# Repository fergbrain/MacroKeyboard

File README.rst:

.. |ss| raw:: html

    <strike>

.. |se| raw:: html

    </strike>
******
README
******

This is the first successful PCB I've designed. I made it as part of `TeachMePCB's <https://www.teachmepcb.com>`_ PCB Layout 101 class.

Everyone in the course made a macrokeypad of some sort. The core "requirements" were:

* 10 MX-style key switches
* 2 Rotary Encoders with RGB leds
* VEML7700 Ambient Light Sensor (I2C)
* NLSF595 LED Driver (SPI)
* 10 NeoPixel lights (1-wire)
* Don't make a rectangular PCB
* Raspberry Pi Pico microcontroller

I made a couple of changes:

* Swapped PCA9745B for NLSF595
* Added ePaper display (because why not make my first project harder)

Required Libraries
==================
* Standard CircuitPython
* Adafruit CircuitPython Library
    * adafruit_hid
    * adafruit_led_animation
    * adafruit_debouncer
    * adafruit_veml7700
    * adafruit_display_text
    * adafruit_button
* `fergcorp_pca9745b <https://github.com/fergbrain/Fergcorp_CircuitPython_PCA9745B>`_
* `fergcorp_pdispectra <https://github.com/fergbrain/Fergcorp_CircuitPython_PDISpectra>`_

Build Notes and Errata:
=======================
For P/N 21-11.03-3, Rev NEW
---------------------------
**Last updated: 2 Feb 2022**

R1 (c5022a6)
^^^^^^^^^^^^

U401 (PI4ULS5V201TAEX), Pin 6:

* IS: Connected to ground.
* SHOULD BE: Connected to 5V+ via a 4.7K ohm resistor

*Note: All annotations on the PCB were also reset and reassigned. However, the original annotation designations are used in this document.*

R2 (fcf9d7e)
^^^^^^^^^^^^
R2404, Pin 03 (SPI_MISO) of U2701 (PCA9745BTWJ)

* IS: Connected to SPI_MISO via R2704 (1k ohm)
* SHOULD BE: No resistor

Pin 27 (SPI_MOSI) of U2701 (PCA9745BTWJ)

* IS: Connected to SPI_MOSI via R2706 (1k ohm)
* SHOULD BE: No resistor

R2707, Pin 26 (SPI_SCLK) of U2701 (PCA9745BTWJ)

* IS: Connected to SPI_SCLK via R2707 (1k ohm)
* SHOULD BE: No resistor

R3 (bb8617a)
^^^^^^^^^^^^
S3001 (Rotary Encoder)

* IS: Pin 01 (red LED) and Pin 04 (blue LED) are swapped
    * S3001 Pin 01 (red LED) goes to U2701 Pin 13 (blue LED)
    * S3001 Pin 04 (blue LED) goes to U2701 Pin 11 (red LED)

* SHOULD BE:

    * S3001 Pin 01 (red LED) connects to 2701 Pin 11 (red LED)
    * S3001 Pin 04 (blue LED) to U2701 Pin 13 (blue LED)

*Note: This has been fixed in software for this version of the PCB*

R4 (3040ea1)
^^^^^^^^^^^^
J2901 (Connector for epaper) Pin 11 (Data/Command) and Pin 09 (Busy)

* IS:

    * U2801 Pin 15 labeled as GPIO12 and connects to J2901 Pin 11
    * U2801 Pin 16 is labeled as GPIO11 and connects to J2901 Pin 09

* SHOULD BE:

    * U2801 Pin 15 labeled as GPIO11 and connects to Pin 09
    * U2801 Pin 16 labeled as GPIO12 and connects to Pin 11

*Note: This has been fixed in software for this version of the PCB*

R5 (51e2212 / 8b634cf)
^^^^^^^^^^^^
* IS: R2901 is 470 ohms
* SHOULD BE: R2901 is 0.47 ohms

|ss| R6 (196a722) |se|
^^^^^^^^^^^^
* |ss|IS: J2901 (Connector for epaper) Pin 10 (Reset) connected to +3.3V via R2902 (100k ohm)|se|
* |ss|SHOULD BE: J2901 Pin 10 connected to U2801 Pin 14 (GPIO10)|se|
|ss|
*Note: This results in SWITCH 4 and ePaper Reset sharing a pin because there are no other pins available. The primary result is that careful context switching needs to managed in software to:*

1.	Deinitialize GPIO10 as an input for SWITCH 4
2.	Setup the ePaper display interface (which uses GPIO10 as an output)
3.	Perform whatever ePaper update is needed
4.	Deinitialze the ePaper interface (which deinitializes GPIO10 as an output)
5.	Re-initialize GPIO10 as an input for SWITCH 4

*Also, while the ePaper is not enabled (i.e. not initialized/reinitialized), GPIO17 (ePaper CS) needs to be set HIGH to prevent the ePaper controller from thinking that data on the SPI line is intended for it.*
|se|

R7 (80c609b)
^^^^^^^^^^^^
* IS: J2901 is Molex P/N 5052782433
* SHOULD BE: J2901 is Amphenol P/N F31L-1A7H1-11024

* IS: Component S201 and S3001 is SparkFun P/N COM-15141
* SHOULD BE: Bournes P/N PEL12T-4225S-S1024

*Note: COM-15141 was originally sourced as an alternate since the Bournes parts weren’t avaible. However, COM-15141 has quality control issues, including the Red LED not working well and the rotary action not registering correctly. SparkFun is aware of these issues.*

R8 (2cafc4d)
^^^^^^^^^^^^
* IS: J2901 (Connector for epaper) Pin 10 (Reset) connected to +3.3V via R2902 (100k ohm)
* SHOULD BE: J2901 Pin 10 connected to U2801 Pin 48 (GPIO25_LED aka TP5)

*Note: This replaces R6 in its entirety.*

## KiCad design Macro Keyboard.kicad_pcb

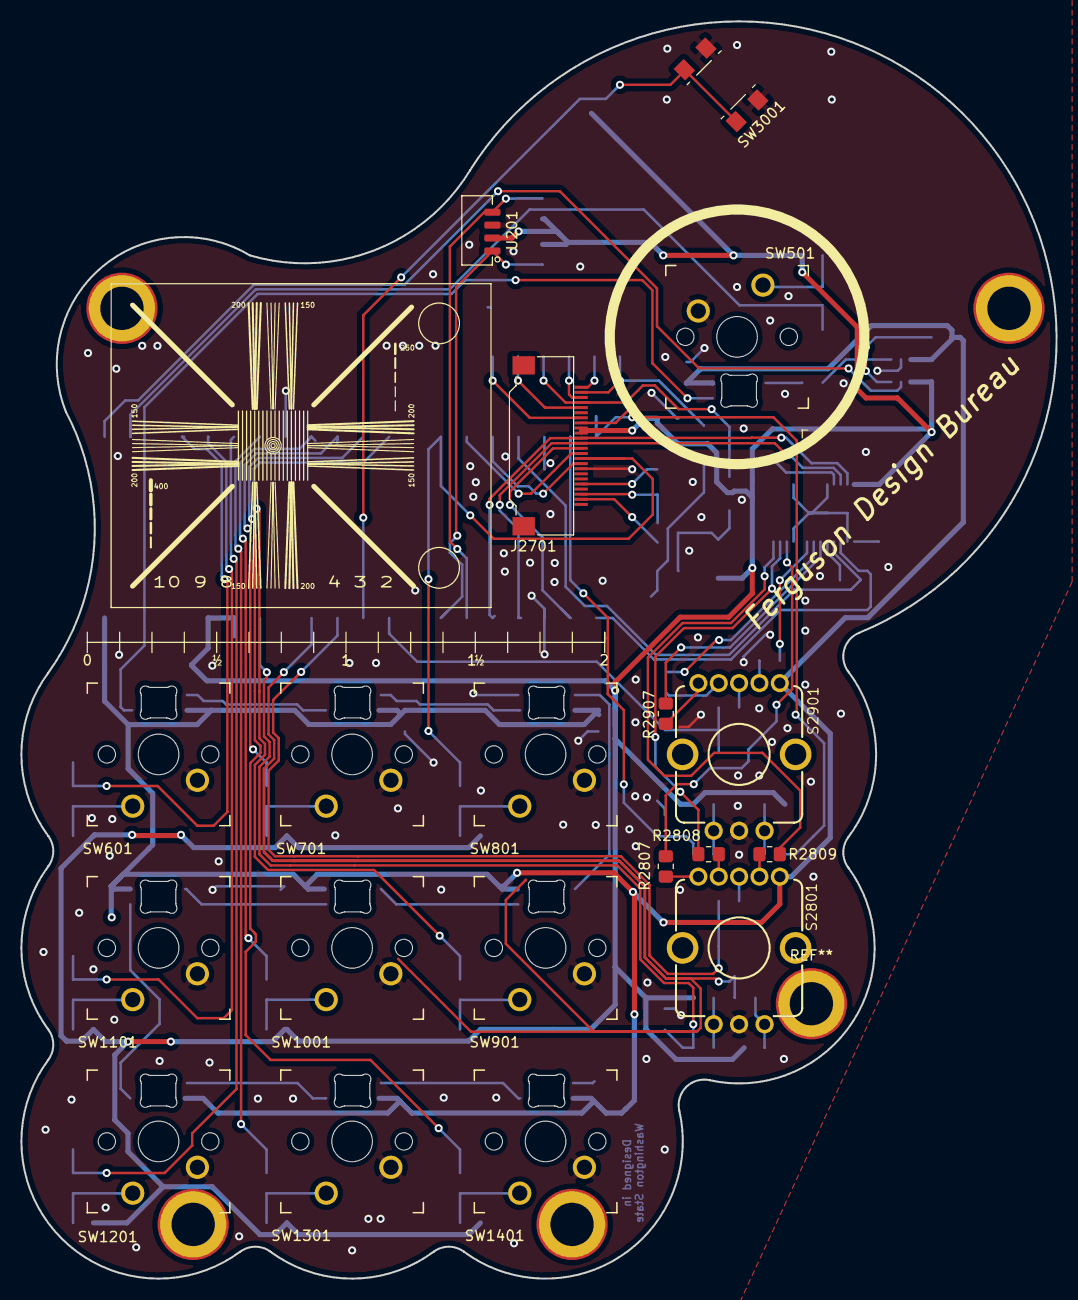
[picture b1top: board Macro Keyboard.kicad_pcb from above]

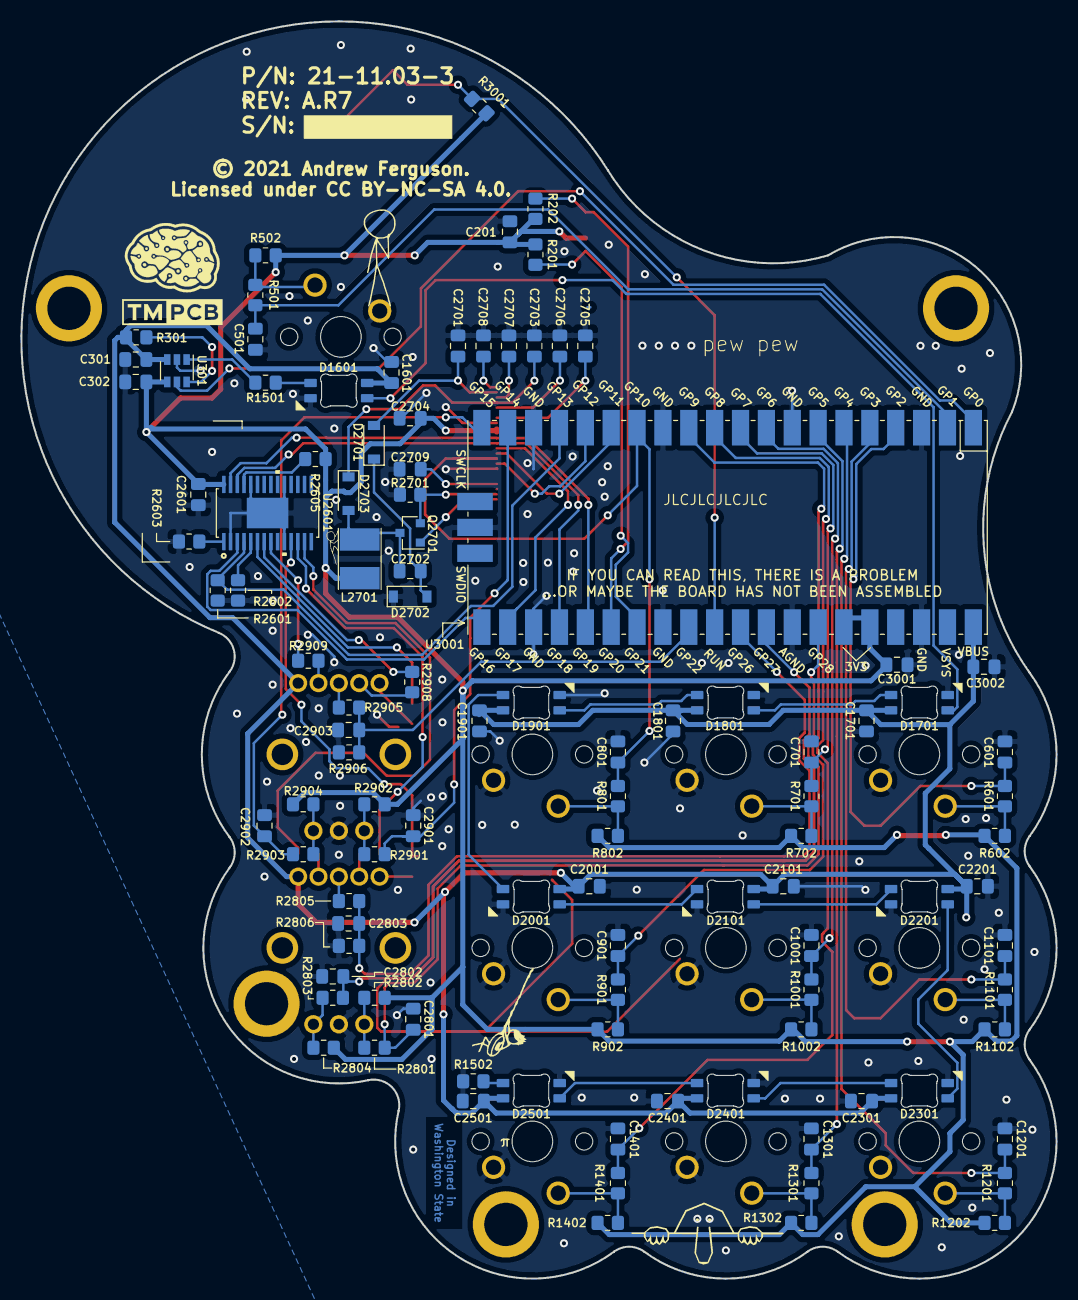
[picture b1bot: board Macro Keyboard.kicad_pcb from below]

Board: 2 copper layers, 101.6 x 123.4 mm, 129 parts (94 on the bottom side), 85 nets.

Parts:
C201, C1601, C1701, C1801, C1901, C2001, C2101, C2201, C2301, C2401, C2501: 10 uF 10% 10V; C_0805_2012Metric_Pad1.18x1.45mm_HandSolder
C301, C302, C501, C601, C701, C801, C901, C1001, C1101, C1201, C1301, C1401, C2601, C2701, C2703, C2704, C2705, C2706, C2707, C2708, C2709, C2801, C2802, C2803, C2901, C2902, C2903, C3001, C3002: 1 uF 10% 10V; C_0805_2012Metric_Pad1.18x1.45mm_HandSolder
C2702: 4.7 uF 10% 10V; C_0805_2012Metric_Pad1.18x1.45mm_HandSolder
D1601, D1701, D1801, D1901, D2301, D2401, D2501: SK6812MINI-E; MX_SK6812MINI-E
D2001, D2101, D2201: SK6812MINI-E; MX_SK6812MINI-E_REV
D2701, D2702, D2703: MBR0530; D_SOD-123
DS**: e-paper_E2154FS091
J2701: FPC 1x24; Amphenol_F31L-1A7H1-11024
L2701: 10 uH 20% 0.8A; L_Taiyo-Yuden_NR-40xx_HandSoldering
Q2701: Q_PJFET_GDS; SOT-23
R201, R202, R301, R501, R601, R701, R801, R901, R1001, R1101, R1201, R1301, R1401, R2601, R2801, R2803, R2806, R2901, R2903, R2906, R3001: 4.7k 5%; R_0805_2012Metric_Pad1.20x1.40mm_HandSolder
R502, R602, R702, R802, R902, R1002, R1102, R1202, R1302, R1402, R2802, R2804, R2902, R2904: 47k 5%; R_0805_2012Metric_Pad1.20x1.40mm_HandSolder
R1501, R2807, R2907: 150 5%; R_0805_2012Metric_Pad1.20x1.40mm_HandSolder
R1502, R2805, R2905: 2.7k 5%; R_0805_2012Metric_Pad1.20x1.40mm_HandSolder
R2602, R2603: 1k 5%; R_0805_2012Metric_Pad1.20x1.40mm_HandSolder
R2605: 100k 5%; R_0805_2012Metric_Pad1.20x1.40mm_HandSolder
R2701: 0.47 5%; R_0805_2012Metric_Pad1.20x1.40mm_HandSolder
R2808, R2809, R2908, R2909: 68 5%; R_0805_2012Metric_Pad1.20x1.40mm_HandSolder
Ref**: Val**; TMPCB Logo bottom silk 10mm
S2801, S2901: ENCODER-RGB-SWITCH; ENCODER_LED_3
SW501, SW601, SW701, SW801, SW901, SW1001, SW1101, SW1201, SW1301, SW1401: KH-PS1611-54; SW_MX
SW3001: SWITCH TACTILE SPST-NO 50MA 12V; SW_SPST_TL3305A
U201: VEML7700; SMD4-X07Y16P127
U301: PI4ULS5V201TAEX; SOT-23-6
U2601: PCA9745BTWJ
U3001: Pico-JER; RPi_Pico_SMD_TH-JER_no_ext_usb
svg2mod: G***; kilroy
svg2mod#2: G***; xkcd-swing
svg2mod#3: G***; xkcd-climb
svg2mod#4: G***; xkcd

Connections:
+3V3: C201.1, C302.2, C2601.2, C2704.2, C3001.1, J2701.15, J2701.16, L2701.1, R201.1, R202.1, R502.1, R602.1, R702.1, R802.1, R902.1, R1002.1, R1102.1, R1202.1, R1302.1, R1402.1, R2605.1, R2802.2, R2804.2, R2902.2, R2904.2, R3001.1, U201.2, U301.4, U2601.28, U3001.35, U3001.36
+5V: C301.1, C1601.2, C1701.2, C1801.2, C1901.2, C2001.2, C2101.2, C2201.2, C2301.2, C2401.2, C2501.2, C3002.1, D1601.1, D1701.1, D1801.1, D1901.1, D2001.1, D2101.1, D2201.1, D2301.1, D2401.1, D2501.1, R301.2, S2801.5, S2901.5, U301.3, U3001.40
/10 Group Switch/Switch 2/SW_RDIV: R601.1, R602.2, SW601.1
/10 Group Switch/Switch 3/SW_RDIV: R701.1, R702.2, SW701.1
/10 Group Switch/Switch 4/SW_RDIV: R801.1, R802.2, SW801.1
/10 Group Switch/Switch 5/SW_RDIV: R901.1, R902.2, SW901.1
/10 Group Switch/Switch 6/SW_RDIV: R1001.1, R1002.2, SW1001.1
/10 Group Switch/Switch 7/SW_RDIV: R1101.1, R1102.2, SW1101.1
/10 Group Switch/Switch 8/SW_RDIV: R1201.1, R1202.2, SW1201.1
/10 Group Switch/Switch 9/SW_RDIV: R1301.1, R1302.2, SW1301.1
/10 Group Switch/Switch 10/SW_RDIV: R1401.1, R1402.2, SW1401.1
/10 Group Switch/Switch_1/SW_RDIV: R501.1, R502.2, SW501.1
/DRIVER_LED_CS: R2601.2, U2601.4, U3001.17
/DS_BUSY_3V3: J2701.9, U3001.16
/DS_CS_3V3: J2701.12, U3001.22
/DS_D_C_3V3: J2701.11, U3001.15
/D_IN_3V3: U301.5, U3001.1
/LED 10/Neo LED 01/D_IN: D1601.4, R1501.1
/LED 10/Neo LED 02/D_IN: D1601.2, D1701.4
/LED 10/Neo LED 03/D_IN: D1701.2, D1801.4
/LED 10/Neo LED 04/D_IN: D1801.2, D1901.4
/LED 10/Neo LED 05/D_IN: D1901.2, D2001.4
/LED 10/Neo LED 06/D_IN: D2001.2, D2101.4
/LED 10/Neo LED 07/D_IN: D2101.2, D2201.4
/LED 10/Neo LED 08/D_IN: D2201.2, D2301.4
/LED 10/Neo LED 09/D_IN: D2301.2, D2401.4
/LED 10/Neo LED 10/D_IN: D2401.2, D2501.4
/LED 10/Neo LED 10/D_OUT: D2501.2, R1502.2
/Level Converter/D_OUT_5V: R1501.2, U301.1
/Pico/RUN_SW: R3001.2, SW3001.1, U3001.30
/REnc_1_A: C2901.1, R2901.1, U3001.19
/REnc_1_B: C2902.2, R2903.1, U3001.20
/REnc_1_SW: C2903.2, R2905.1, R2906.2, U3001.29
/REnc_2_A: C2801.1, R2801.1, U3001.34
/REnc_2_B: C2802.2, R2803.1, U3001.32
/REnc_2_SW: C2803.2, R2805.1, R2806.2, U3001.31
/RGB Driver/DRIVER_LED_SW1_B_5V: R2909.1, U2601.8
/RGB Driver/DRIVER_LED_SW1_G_5V: R2908.1, U2601.7
/RGB Driver/DRIVER_LED_SW1_R_5V: R2907.1, U2601.6
/RGB Driver/DRIVER_LED_SW2_B_5V: R2809.1, U2601.13
/RGB Driver/DRIVER_LED_SW2_G_5V: R2808.1, U2601.12
/RGB Driver/DRIVER_LED_SW2_R_5V: R2807.1, U2601.11
/Rotary Encoder 1/RES_DB: R2909.2, S2901.4
/Rotary Encoder 1/RES_DG: R2908.2, S2901.2
/Rotary Encoder 1/RES_DR: R2907.2, S2901.1
/Rotary Encoder 1/RE_SW_A: R2901.2, R2902.1, S2901.A
/Rotary Encoder 1/RE_SW_B: R2903.2, R2904.1, S2901.B
/Rotary Encoder 1/RE_SW_RES: R2905.2, S2901.3
/Rotary Encoder 2/RES_DB: R2809.2, S2801.4
/Rotary Encoder 2/RES_DG: R2808.2, S2801.2
/Rotary Encoder 2/RES_DR: R2807.2, S2801.1
/Rotary Encoder 2/RE_SW_A: R2801.2, R2802.1, S2801.A
/Rotary Encoder 2/RE_SW_B: R2803.2, R2804.1, S2801.B
/Rotary Encoder 2/RE_SW_RES: R2805.2, S2801.3
/SCL: R201.2, U201.1, U3001.27
/SDA: R202.2, U201.4, U3001.26
/SW1: C501.1, R501.2, U3001.2
/SW2: C601.1, R601.2, U3001.4
/SW3: C701.1, R701.2, U3001.10
/SW4: C801.1, J2701.10, R801.2, U3001.14
/SW5: C901.1, R901.2, U3001.12
/SW6: C1001.1, R1001.2, U3001.9
/SW7: C1101.1, R1101.2, U3001.5
/SW8: C1201.1, R1201.2, U3001.6
/SW9: C1301.1, R1301.2, U3001.7
/SW10: C1401.1, R1401.2, U3001.11
/eInk Display/DS_GDR: J2701.2, Q2701.1
/eInk Display/DS_MOSFET_D: J2701.3, Q2701.2, R2701.1
/eInk Display/DS_MOSFET_S: C2702.1, D2703.2, L2701.2, Q2701.3
/eInk Display/DS_VCOM: C2708.2, J2701.24
/eInk Display/DS_VDDD: C2705.2, J2701.18
/eInk Display/DS_VDHR: C2709.2, J2701.5
/eInk Display/DS_VGH: C2703.1, D2703.1, J2701.21
/eInk Display/DS_VGL: C2701.1, D2701.2, J2701.23
/eInk Display/DS_VSH: C2706.1, J2701.20
/eInk Display/DS_VSL: C2707.2, J2701.22
GND: C201.2, C301.2, C302.1, C501.2, C601.2, C701.2, C801.2, C901.2, C1001.2, C1101.2, C1201.2, C1301.2, C1401.2, C1601.1, C1701.1, C1801.1, C1901.1, C2001.1, C2101.1, C2201.1, C2301.1, C2401.1, C2501.1, C2601.1, C2701.2, C2703.2, C2704.1, C2705.1, C2706.2, C2707.1, C2708.1, C2709.1, C2801.2, C2802.1, C2803.1, C2901.2, C2902.1, C2903.1, C3001.2, C3002.2, D1601.3, D1701.3, D1801.3, D1901.3, D2001.3, D2101.3, D2201.3, D2301.3, D2401.3, D2501.3, D2702.1, J2701.8, J2701.17, R1502.1, R2601.1, R2602.1, R2603.2, R2701.2, R2806.1, R2906.1, S2801.C, S2901.C, SW501.2, SW601.2, SW701.2, SW801.2, SW901.2, SW1001.2, SW1101.2, SW1201.2, SW1301.2, SW1401.2, SW3001.2, U201.3, U301.2, U2601.2, U2601.10, U2601.19, U2601.24, U2601.EPAD, U3001.3, U3001.8, U3001.13, U3001.18, U3001.23, U3001.28, U3001.33, U3001.38, U3001.42
unnamed: C2702.2, D2701.1, D2702.2
unnamed: R301.1, U301.6
unnamed: R2602.2, U2601.5
unnamed: R2603.1, U2601.1
unnamed: R2605.2, U2601.25
SPI_MISO_3V: U2601.3, U3001.21
SPI_MOSI_3V: J2701.14, U2601.27, U3001.25
SPI_SCLK_3V: J2701.13, U2601.26, U3001.24

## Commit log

2021-11-27 Intial commit
2021-11-27 Added PCA9745B16B. Updated schematic. ERC Passes.
2021-11-27 Cleanup
2021-11-27 fixed broken schematics becuase of deleted rescue files. ECA passes.
2021-11-27 initial layout
2021-11-29 Checkpoint
2021-11-29 Switch NeoPixel to SK6812MINI-E
2021-11-29 design checkpoint
2021-11-30 Starting routing
2021-12-01 Layout completed. Design check passes.
2021-12-04 Moved everything to the back that I wanted. Added fun things :)
2021-12-04 Cleanup autosave
2021-12-04 add .gitignore file
2021-12-04 Update Pads Mask Clearance to Oshpark requirements
2021-12-05 Updated silkscreen outlines. Added epaper cad part.
2021-12-05 don't track gerber exports
2021-12-06 Add Solder Mask Clearance
2021-12-06 Move D2903 to allow for extra clearance
2021-12-06 Update GND connection on J2901 to remove sliver
2021-12-06 Updated several part orientations to eliminate minimuim clearance issues.
2021-12-06 Updated routing to eliminate minimuim clearance issues.
2021-12-06 Added labels
2021-12-07 Add net labels and update PCB
2021-12-07 Re-arrange pins and cleanup routing
2021-12-07 Set all B.SilkS references to 0.8mm height and width
2021-12-07 Routing tweaks
2021-12-07 Tweak trace routings
2021-12-11 Flipped pins on J2901 to be 24-1 instead of 1-24
2021-12-13 Change J2901 to Amphenon connector
2021-12-13 Added estop stp and Marks comments from DFM check
2021-12-13 Add JLC P/N locator text
2021-12-13 singular e-stop cad file
2022-01-06 Fix design error in PI4ULS5V201TAEX. Reset and reassigned all annotations.
2022-01-07 Remove resistor for SPI MOSI, MISO, and CS for LED Driver
2022-01-09 Fixed wiring for rotary encoder 2. R and B pins were swapped.
2022-01-12 Assignments for Pico GPIO 11 and 12 were flipped. Fixed.
2022-01-19 R2701 should be 0.47 ohm...not 470 ohm
2022-01-28 Updated so that eink reset pin is shared with GP04. Not ideal, but should work.
2022-01-29 Start Tracking
2022-01-30 Made a class and tictactoe game
2022-02-01 Checkpoint for buttons vs labels
2022-02-02 Updated Switch to use Bournes P/N PEL12T-4225S-S1024, Update Connector to use Amphenol F31L-1A7H1-11024
2022-02-02 Use GP25_LED for ePaper RESET
    Note: This replaces R6/196a722 in its entirety.
    IS: J2901 (Connector for epaper) Pin 10 (Reset) connected to +3.3V via R2902 (100k ohm)
    SHOULD BE: J2901 Pin 10 connected to U2801 Pin 48 (GPIO25_LED aka TP5)
2022-02-03 Feature complete...basically. Still needs lots of cleanup, but I'm declaring it done.
2022-02-03 Gave life to tic tac toe
2022-02-03 formatted with black
2022-02-03 Formatting, cleanup, and LICENSE
2022-02-03 Move files to hardware subfolder
2022-02-03 Add README.rst with build notes/errata
2022-02-03 Update license file
2022-02-03 Add background info...will need to add photos later
2022-02-03 Added reqired libraries
2022-02-03 Added images
2022-02-03 Update ignored files/directories
2022-02-03 Fix formatting
2022-02-04 Fix logic bug for game. Set starting state to be admin screen.
2022-02-04 Set epaper enabled (typically disabled for debugging)
2022-02-05 Fix typo

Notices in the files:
Macro Keyboard.kicad_pcb:
© 2021 Andrew Ferguson.
Licensed under CC BY-NC-SA 4.0.
parts and their libraries:
Copyright 2021 Accelerated Designs. All rights reserved.
